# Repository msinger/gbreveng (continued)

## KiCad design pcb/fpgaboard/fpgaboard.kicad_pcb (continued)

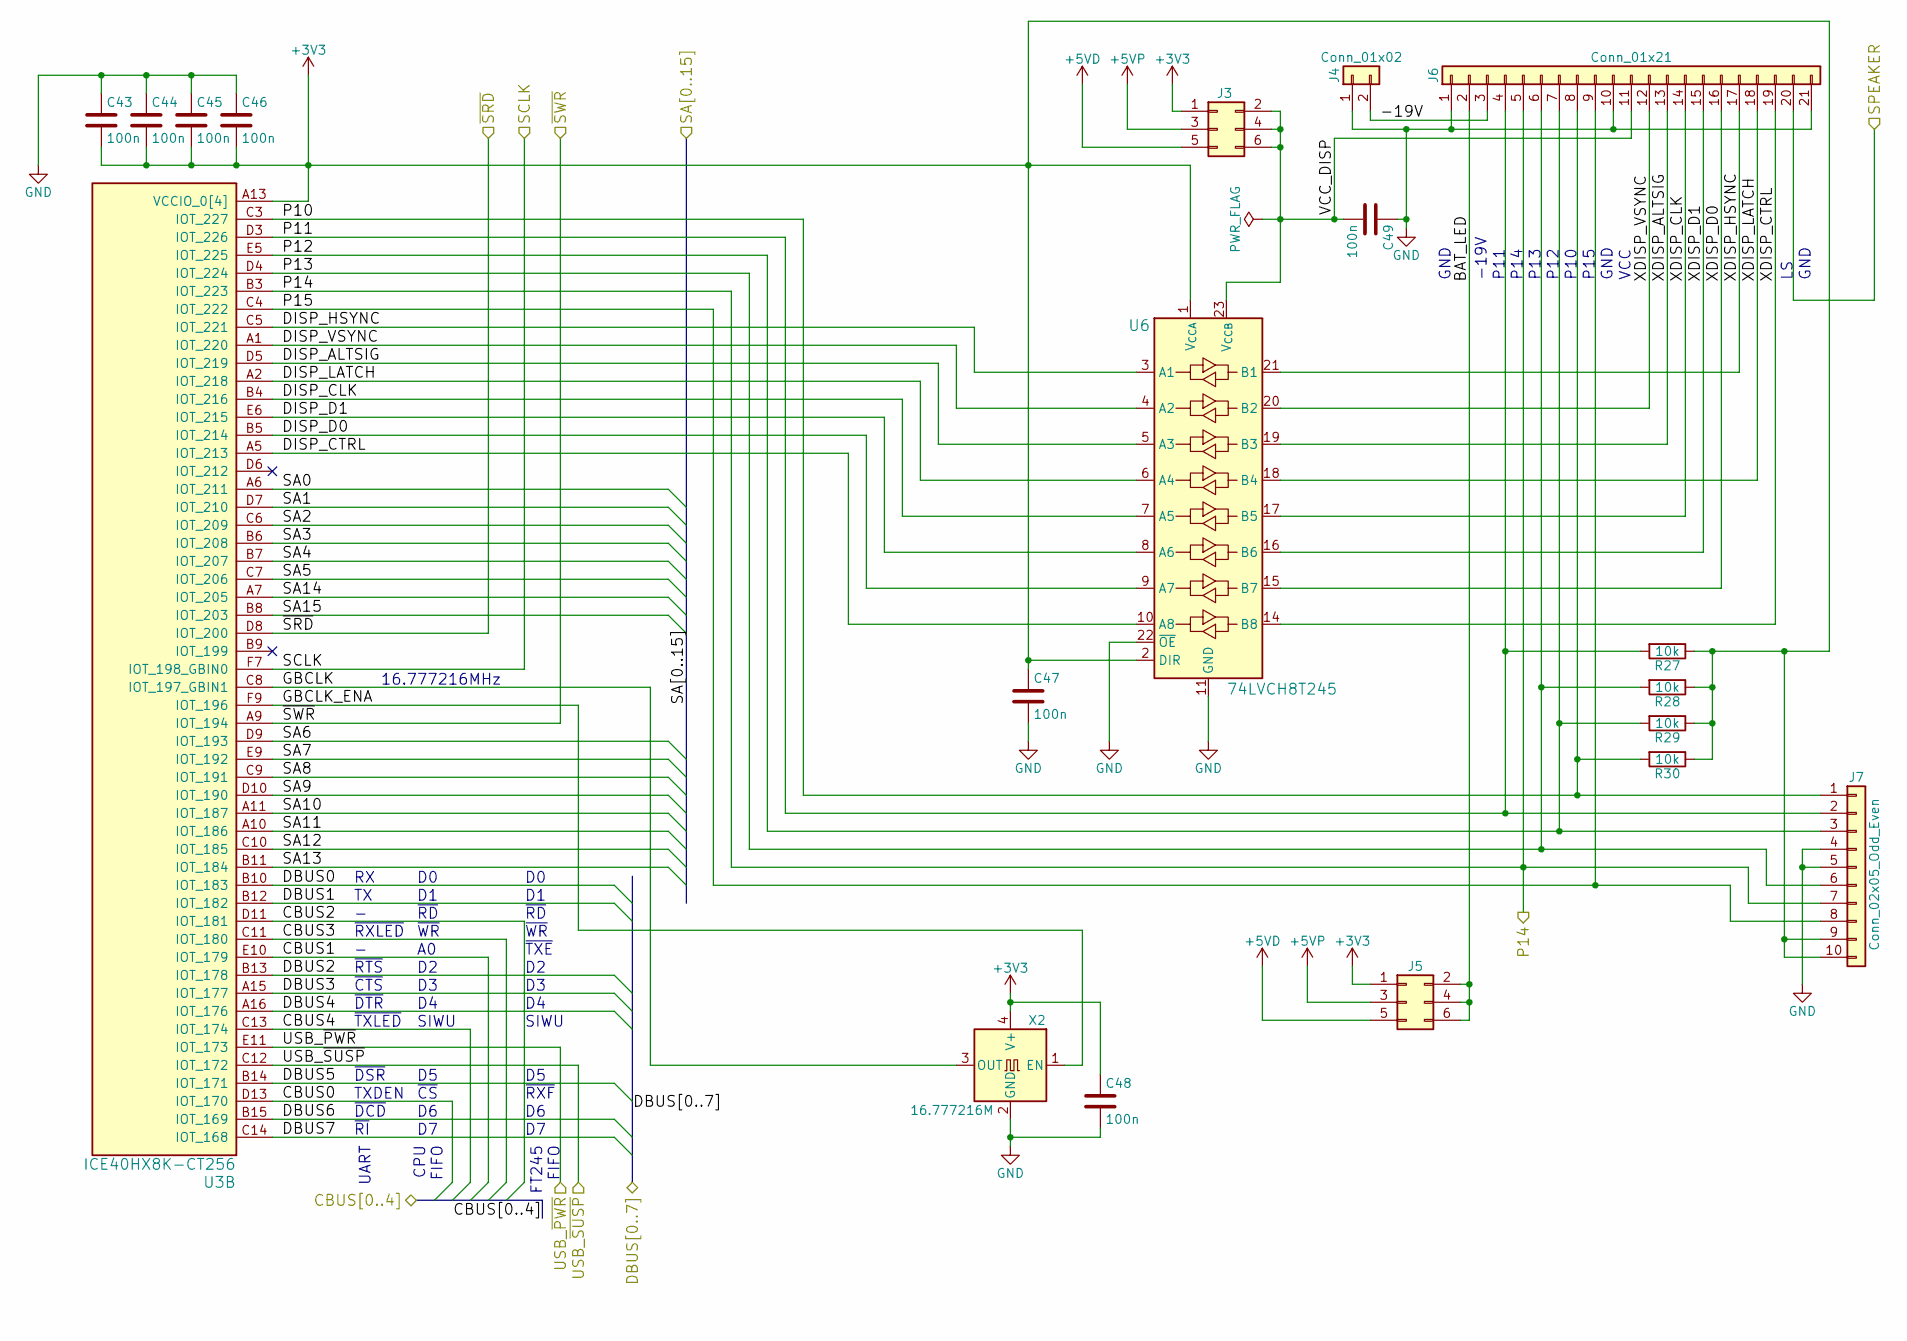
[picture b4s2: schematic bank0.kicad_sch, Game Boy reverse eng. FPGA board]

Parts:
C43, C44, C45, C46, C47, C48, C49: 100n; C_0402_1005Metric_Pad0.74x0.62mm_HandSolder
J3, J5: Conn_02x03_Odd_Even; PinHeader_2x03_P2.54mm_Vertical
J4: Conn_01x02; PinHeader_1x02_P2.54mm_Vertical
J6: Conn_01x21; DMG_FFC_LCD-Board_21Pin
J7: Conn_02x05_Odd_Even; PinHeader_2x05_P2.54mm_Vertical
R27, R28, R29, R30: 10k; R_0402_1005Metric
U3: ICE40HX8K-CT256; BGA-256_14.0x14.0mm_Layout16x16_P0.8mm_Ball0.45mm_Pad0.32mm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
U6: 74LVCH8T245; TSSOP-24_4.4x7.8mm_P0.65mm
X2: 16.777216M; Oscillator_SMD_EuroQuartz_XO32-4Pin_3.2x2.5mm_HandSoldering

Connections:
+3V3: C43.2, C44.2, C45.2, C46.2, C47.1, C48.1, J3.1, J5.1, J7.9, J7.10, R27.1, R28.1, R29.1, R30.1, U3.A3 (VCCIO_0[4]), U3.A8 (VCCIO_0[4]), U3.A13 (VCCIO_0[4]), U3.F8 (VCCIO_0[4]), U6.1 (V_{CCA}), U6.2 (DIR), X2.4 (V+); also elsewhere on the board
+5VD: J3.5, J5.5; also elsewhere on the board
+5VP: J3.3, J5.3; also elsewhere on the board
/Audio/SPEAKER: J6.20; also elsewhere on the board
/Bank0: Display, Keyboard, Clock/-19V: J4.2, J6.3
/Bank0: Display, Keyboard, Clock/A0: U3.A6 (IOT_211); also elsewhere on the board
/Bank0: Display, Keyboard, Clock/A1: U3.D7 (IOT_210); also elsewhere on the board
/Bank0: Display, Keyboard, Clock/A2: U3.C6 (IOT_209); also elsewhere on the board
/Bank0: Display, Keyboard, Clock/A3: U3.B6 (IOT_208); also elsewhere on the board
/Bank0: Display, Keyboard, Clock/A4: U3.B7 (IOT_207); also elsewhere on the board
/Bank0: Display, Keyboard, Clock/A5: U3.C7 (IOT_206); also elsewhere on the board
/Bank0: Display, Keyboard, Clock/A6: U3.D9 (IOT_193); also elsewhere on the board
/Bank0: Display, Keyboard, Clock/A7: U3.E9 (IOT_192); also elsewhere on the board
/Bank0: Display, Keyboard, Clock/A8: U3.C9 (IOT_191); also elsewhere on the board
/Bank0: Display, Keyboard, Clock/A9: U3.D10 (IOT_190); also elsewhere on the board
/Bank0: Display, Keyboard, Clock/A10: U3.A11 (IOT_187); also elsewhere on the board
/Bank0: Display, Keyboard, Clock/A11: U3.A10 (IOT_186); also elsewhere on the board
/Bank0: Display, Keyboard, Clock/A12: U3.C10 (IOT_185); also elsewhere on the board
/Bank0: Display, Keyboard, Clock/A13: U3.B11 (IOT_184); also elsewhere on the board
/Bank0: Display, Keyboard, Clock/A14: U3.A7 (IOT_205); also elsewhere on the board
/Bank0: Display, Keyboard, Clock/A15: U3.B8 (IOT_203); also elsewhere on the board
/Bank0: Display, Keyboard, Clock/BAT_LED: J5.2, J5.4, J5.6, J6.2
/Bank0: Display, Keyboard, Clock/CART_SL_CLK: U3.F7 (IOT_198_GBIN0); also elsewhere on the board
/Bank0: Display, Keyboard, Clock/CART_SL_~RD: U3.D8 (IOT_200); also elsewhere on the board
/Bank0: Display, Keyboard, Clock/CART_SL_~WR: U3.A9 (IOT_194); also elsewhere on the board
/Bank0: Display, Keyboard, Clock/CBUS0: U3.D13 (IOT_170); also elsewhere on the board
/Bank0: Display, Keyboard, Clock/CBUS1: U3.E10 (IOT_179); also elsewhere on the board
/Bank0: Display, Keyboard, Clock/CBUS2: U3.D11 (IOT_181); also elsewhere on the board
/Bank0: Display, Keyboard, Clock/CBUS3: U3.C11 (IOT_180); also elsewhere on the board
/Bank0: Display, Keyboard, Clock/CBUS4: U3.C13 (IOT_174); also elsewhere on the board
/Bank0: Display, Keyboard, Clock/DBUS0: U3.B10 (IOT_183); also elsewhere on the board
/Bank0: Display, Keyboard, Clock/DBUS1: U3.B12 (IOT_182); also elsewhere on the board
/Bank0: Display, Keyboard, Clock/DBUS2: U3.B13 (IOT_178); also elsewhere on the board
/Bank0: Display, Keyboard, Clock/DBUS3: U3.A15 (IOT_177); also elsewhere on the board
/Bank0: Display, Keyboard, Clock/DBUS4: U3.A16 (IOT_176); also elsewhere on the board
/Bank0: Display, Keyboard, Clock/DBUS5: U3.B14 (IOT_171); also elsewhere on the board
/Bank0: Display, Keyboard, Clock/DBUS6: U3.B15 (IOT_169); also elsewhere on the board
/Bank0: Display, Keyboard, Clock/DBUS7: U3.C14 (IOT_168); also elsewhere on the board
/Bank0: Display, Keyboard, Clock/DISP_ALTSIG: U3.D5 (IOT_219), U6.5 (A3)
/Bank0: Display, Keyboard, Clock/DISP_CLK: U3.B4 (IOT_216), U6.7 (A5)
/Bank0: Display, Keyboard, Clock/DISP_CTRL: U3.A5 (IOT_213), U6.10 (A8)
/Bank0: Display, Keyboard, Clock/DISP_D0: U3.B5 (IOT_214), U6.9 (A7)
/Bank0: Display, Keyboard, Clock/DISP_D1: U3.E6 (IOT_215), U6.8 (A6)
/Bank0: Display, Keyboard, Clock/DISP_HSYNC: U3.C5 (IOT_221), U6.3 (A1)
/Bank0: Display, Keyboard, Clock/DISP_LATCH: U3.A2 (IOT_218), U6.6 (A4)
/Bank0: Display, Keyboard, Clock/DISP_VSYNC: U3.A1 (IOT_220), U6.4 (A2)
/Bank0: Display, Keyboard, Clock/GBCLK: U3.C8 (IOT_197_GBIN1), X2.3 (OUT)
/Bank0: Display, Keyboard, Clock/GBCLK_ENA: U3.F9 (IOT_196), X2.1 (EN)
/Bank0: Display, Keyboard, Clock/P10: J6.8, J7.1, R30.2, U3.C3 (IOT_227)
/Bank0: Display, Keyboard, Clock/P11: J6.4, J7.2, R27.2, U3.D3 (IOT_226)
/Bank0: Display, Keyboard, Clock/P12: J6.7, J7.3, R29.2, U3.E5 (IOT_225)
/Bank0: Display, Keyboard, Clock/P13: J6.6, J7.6, R28.2, U3.D4 (IOT_224)
/Bank0: Display, Keyboard, Clock/P14: J6.5, J7.7, U3.B3 (IOT_223); also elsewhere on the board
/Bank0: Display, Keyboard, Clock/P15: J6.9, J7.8, U3.C4 (IOT_222)
/Bank0: Display, Keyboard, Clock/USB_~PWR: U3.E11 (IOT_173); also elsewhere on the board
/Bank0: Display, Keyboard, Clock/USB_~SUSP: U3.C12 (IOT_172); also elsewhere on the board
/Bank0: Display, Keyboard, Clock/VCC_DISP: C49.2, J3.2, J3.4, J3.6, J6.11, U6.23 (V_{CCB}), U6.24 (V_{CCB})
/Bank0: Display, Keyboard, Clock/XDISP_ALTSIG: J6.13, U6.19 (B3)
/Bank0: Display, Keyboard, Clock/XDISP_CLK: J6.14, U6.17 (B5)
/Bank0: Display, Keyboard, Clock/XDISP_CTRL: J6.19, U6.14 (B8)
/Bank0: Display, Keyboard, Clock/XDISP_D0: J6.16, U6.15 (B7)
/Bank0: Display, Keyboard, Clock/XDISP_D1: J6.15, U6.16 (B6)
/Bank0: Display, Keyboard, Clock/XDISP_HSYNC: J6.17, U6.21 (B1)
/Bank0: Display, Keyboard, Clock/XDISP_LATCH: J6.18, U6.18 (B4)
/Bank0: Display, Keyboard, Clock/XDISP_VSYNC: J6.12, U6.20 (B2)
GND: C43.1, C44.1, C45.1, C46.1, C47.2, C48.2, C49.1, J4.1, J6.1, J6.10, J6.21, J7.4, J7.5, U6.11 (GND), U6.12 (GND), U6.13 (GND), U6.22 (~OE), X2.2 (GND); also elsewhere on the board

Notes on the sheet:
~{TXLED}
~{WR}
~{RXLED}
~{RI}
CPU FIFO
SIWU
16.777216MHz
P11
P12
-19V
VCC
FT245 FIFO
GND
~{DSR}
~{RTS}
~{DCD}
~{DTR}
P14
~{CTS}
P15
UART
~{RD}
~{CS}
TXDEN
~{RXF}
~{TXE}
P13
P10

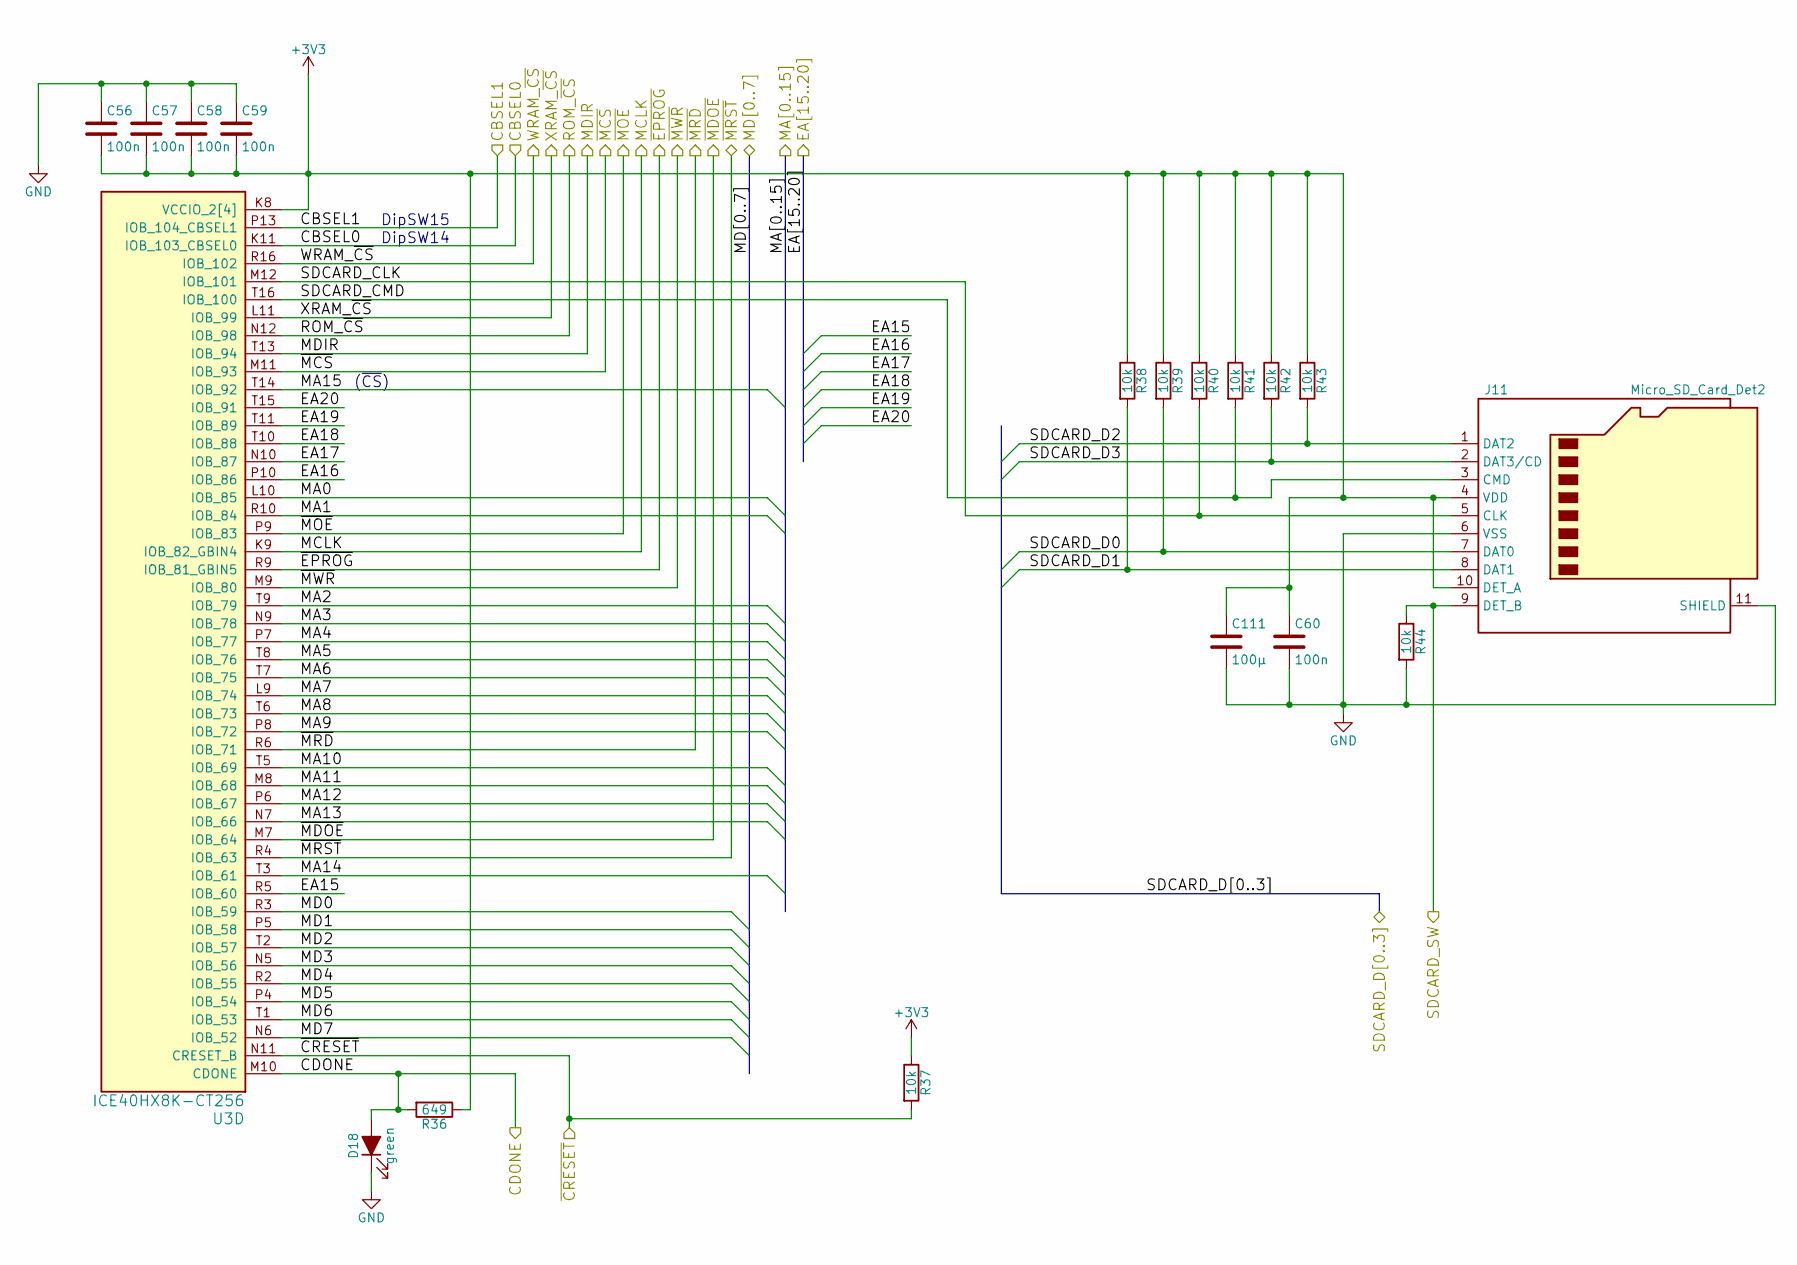
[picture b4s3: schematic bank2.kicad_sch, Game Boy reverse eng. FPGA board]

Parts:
C56, C57, C58, C59, C60: 100n; C_0402_1005Metric_Pad0.74x0.62mm_HandSolder
C111: 100µ; C_1206_3216Metric
D18: green; LED_0805_2012Metric_Pad1.15x1.40mm_HandSolder
J11: Micro_SD_Card_Det2; microSD_HC_Hirose_DM3AT-SF-PEJM5
R36: 649; R_0402_1005Metric
R37, R38, R39, R40, R41, R42, R43, R44: 10k; R_0402_1005Metric
U3: ICE40HX8K-CT256; BGA-256_14.0x14.0mm_Layout16x16_P0.8mm_Ball0.45mm_Pad0.32mm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

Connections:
+3V3: C56.2, C57.2, C58.2, C59.2, C60.1, C111.1, J11.4 (VDD), J11.10 (DET_A), R36.1, R37.1, R38.1, R39.1, R40.1, R41.1, R42.1, R43.1, U3.K8 (VCCIO_2[4]), U3.P3 (VCCIO_2[4]), U3.R8 (VCCIO_2[4]), U3.R13 (VCCIO_2[4]); also elsewhere on the board
/Bank1: GPIOA/SDCARD_SW: J11.9 (DET_B), R44.1; also elsewhere on the board
/Bank2: SDCard/CART_MA_CLK: U3.K9 (IOB_82_GBIN4); also elsewhere on the board
/Bank2: SDCard/CART_MA_DIR: U3.T13 (IOB_94); also elsewhere on the board
/Bank2: SDCard/CART_MA_~CS: U3.M11 (IOB_93); also elsewhere on the board
/Bank2: SDCard/CART_MA_~OE: U3.P9 (IOB_83); also elsewhere on the board
/Bank2: SDCard/CART_MA_~OE~_DATA: U3.M7 (IOB_64); also elsewhere on the board
/Bank2: SDCard/CART_MA_~RST: U3.R4 (IOB_63); also elsewhere on the board
/Bank2: SDCard/CBSEL0: U3.K11 (IOB_103_CBSEL0); also elsewhere on the board
/Bank2: SDCard/CBSEL1: U3.P13 (IOB_104_CBSEL1); also elsewhere on the board
/Bank2: SDCard/CDONE: D18.2 (A), R36.2, U3.M10 (CDONE); also elsewhere on the board
/Bank2: SDCard/EA15: U3.R5 (IOB_60); also elsewhere on the board
/Bank2: SDCard/EA16: U3.P10 (IOB_86); also elsewhere on the board
/Bank2: SDCard/EA17: U3.N10 (IOB_87); also elsewhere on the board
/Bank2: SDCard/EA18: U3.T10 (IOB_88); also elsewhere on the board
/Bank2: SDCard/EA19: U3.T11 (IOB_89); also elsewhere on the board
/Bank2: SDCard/EA20: U3.T15 (IOB_91); also elsewhere on the board
/Bank2: SDCard/MA0: U3.L10 (IOB_85); also elsewhere on the board
/Bank2: SDCard/MA1: U3.R10 (IOB_84); also elsewhere on the board
/Bank2: SDCard/MA2: U3.T9 (IOB_79); also elsewhere on the board
/Bank2: SDCard/MA3: U3.N9 (IOB_78); also elsewhere on the board
/Bank2: SDCard/MA4: U3.P7 (IOB_77); also elsewhere on the board
/Bank2: SDCard/MA5: U3.T8 (IOB_76); also elsewhere on the board
/Bank2: SDCard/MA6: U3.T7 (IOB_75); also elsewhere on the board
/Bank2: SDCard/MA7: U3.L9 (IOB_74); also elsewhere on the board
/Bank2: SDCard/MA8: U3.T6 (IOB_73); also elsewhere on the board
/Bank2: SDCard/MA9: U3.P8 (IOB_72); also elsewhere on the board
/Bank2: SDCard/MA10: U3.T5 (IOB_69); also elsewhere on the board
/Bank2: SDCard/MA11: U3.M8 (IOB_68); also elsewhere on the board
/Bank2: SDCard/MA12: U3.P6 (IOB_67); also elsewhere on the board
/Bank2: SDCard/MA13: U3.N7 (IOB_66); also elsewhere on the board
/Bank2: SDCard/MA14: U3.T3 (IOB_61); also elsewhere on the board
/Bank2: SDCard/MA15: U3.T14 (IOB_92); also elsewhere on the board
/Bank2: SDCard/MD0: U3.R3 (IOB_59); also elsewhere on the board
/Bank2: SDCard/MD1: U3.P5 (IOB_58); also elsewhere on the board
/Bank2: SDCard/MD2: U3.T2 (IOB_57); also elsewhere on the board
/Bank2: SDCard/MD3: U3.N5 (IOB_56); also elsewhere on the board
/Bank2: SDCard/MD4: U3.R2 (IOB_55); also elsewhere on the board
/Bank2: SDCard/MD5: U3.P4 (IOB_54); also elsewhere on the board
/Bank2: SDCard/MD6: U3.T1 (IOB_53); also elsewhere on the board
/Bank2: SDCard/MD7: U3.N6 (IOB_52); also elsewhere on the board
/Bank2: SDCard/ONBRD_~PROG: U3.R9 (IOB_81_GBIN5); also elsewhere on the board
/Bank2: SDCard/ROM_~CS: U3.N12 (IOB_98); also elsewhere on the board
/Bank2: SDCard/SD0: J11.7 (DAT0), R39.2; also elsewhere on the board
/Bank2: SDCard/SD1: J11.8 (DAT1), R38.2; also elsewhere on the board
/Bank2: SDCard/SD2: J11.1 (DAT2), R43.2; also elsewhere on the board
/Bank2: SDCard/SD3: J11.2 (DAT3/CD), R42.2; also elsewhere on the board
/Bank2: SDCard/SDCARD_CLK: J11.5 (CLK), R40.2, U3.M12 (IOB_101)
/Bank2: SDCard/SDCARD_CMD: J11.3 (CMD), R41.2, U3.T16 (IOB_100)
/Bank2: SDCard/WRAM_~CS: U3.R16 (IOB_102); also elsewhere on the board
/Bank2: SDCard/XRAM_~CS: U3.L11 (IOB_99); also elsewhere on the board
/Bank2: SDCard/~CRESET: R37.2, U3.N11 (CRESET_B); also elsewhere on the board
/~MRD: U3.R6 (IOB_71); also elsewhere on the board
/~MWR: U3.M9 (IOB_80); also elsewhere on the board
GND: C56.1, C57.1, C58.1, C59.1, C60.2, C111.2, D18.1 (K), J11.6 (VSS), J11.11 (SHIELD), R44.2; also elsewhere on the board

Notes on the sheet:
DipSW14
(~{CS})
DipSW15

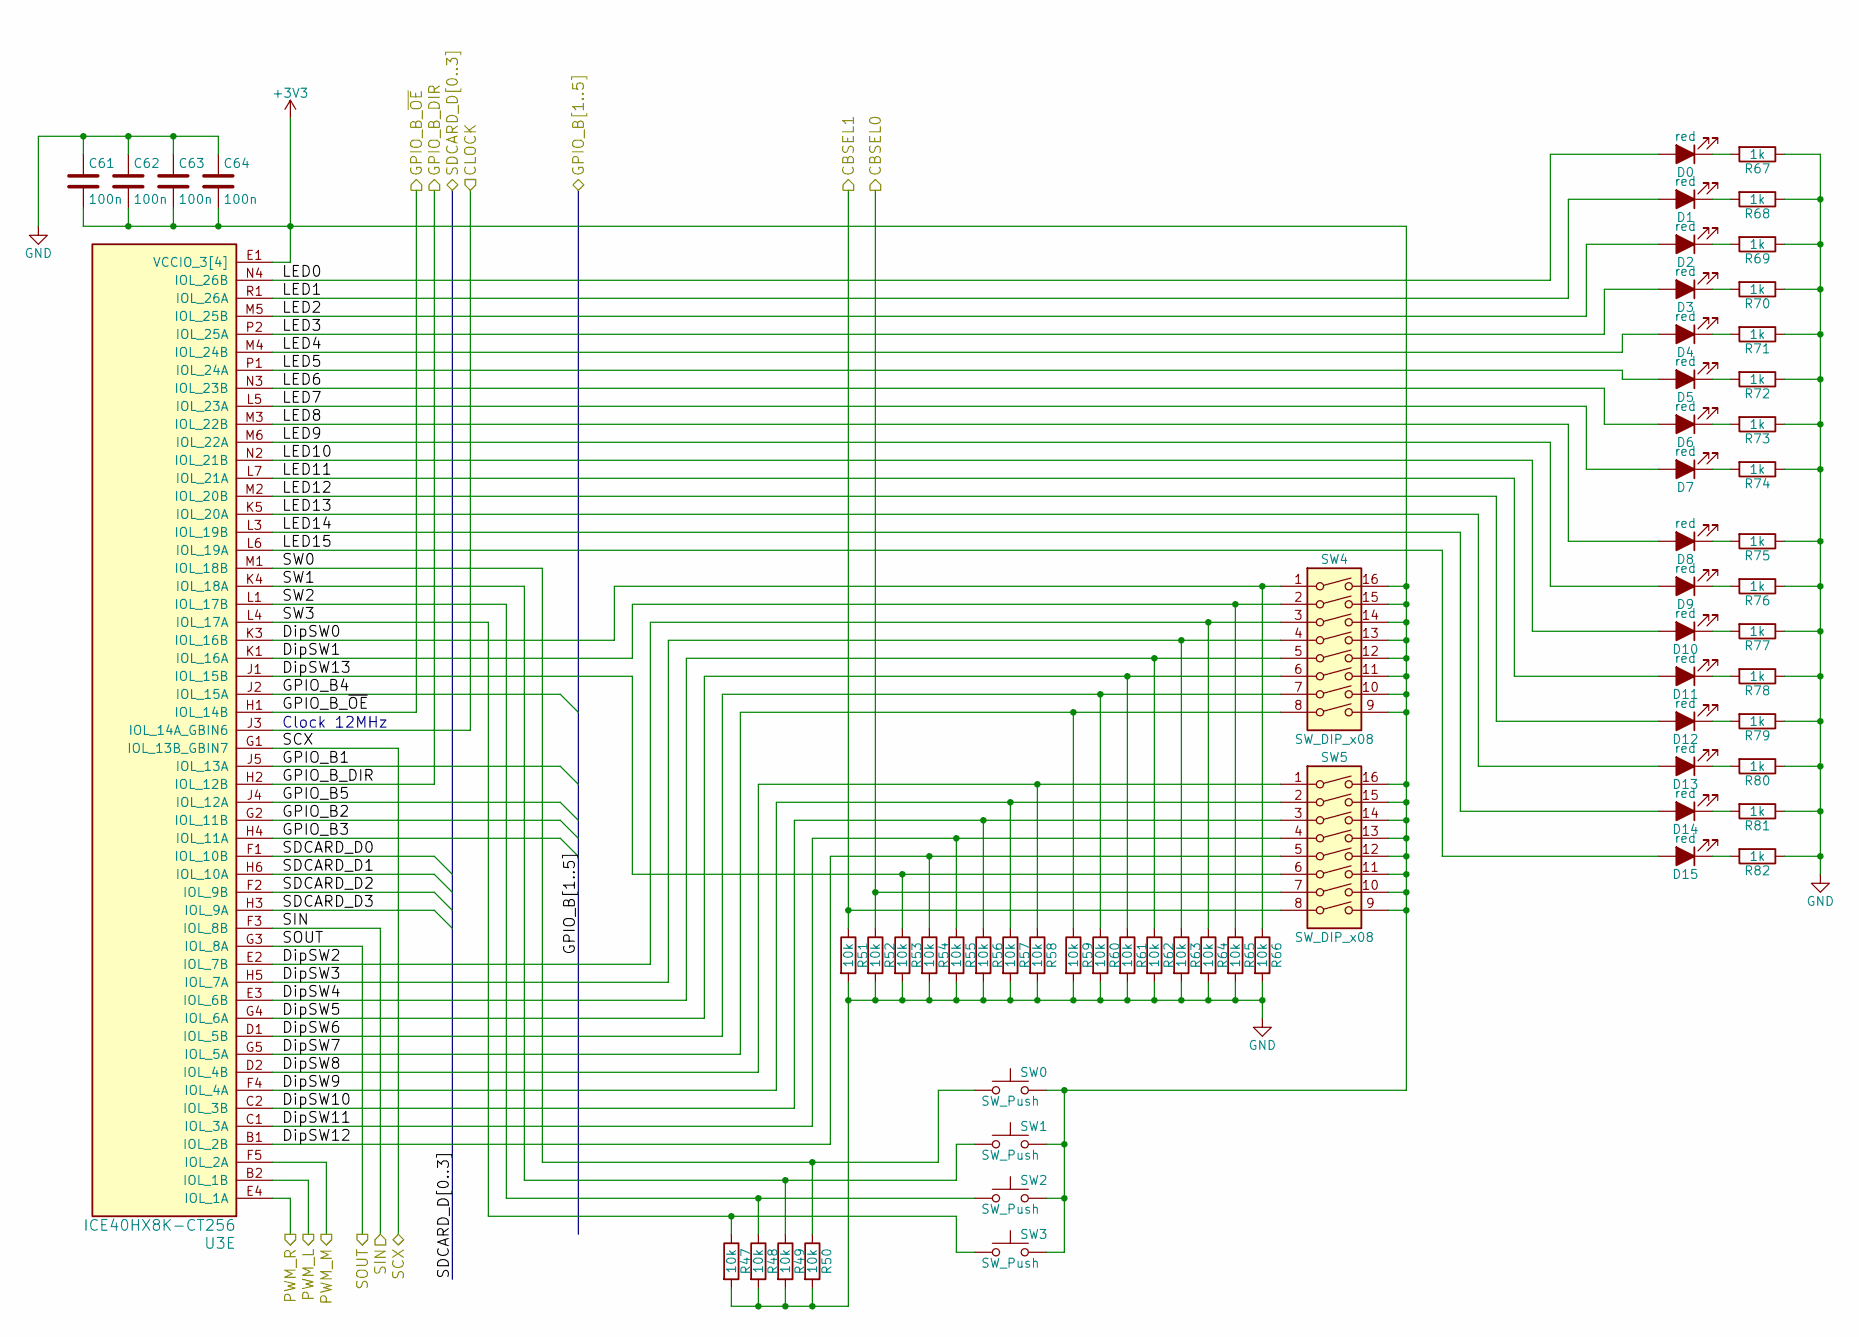
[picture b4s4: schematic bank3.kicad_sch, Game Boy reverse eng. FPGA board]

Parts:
C61, C62, C63, C64: 100n; C_0402_1005Metric_Pad0.74x0.62mm_HandSolder
D0, D1, D2, D3, D4, D5, D6, D7, D8, D9, D10, D11, D12, D13, D14, D15: red; LED_0805_2012Metric_Pad1.15x1.40mm_HandSolder
R47, R48, R49, R50, R51, R52, R53, R54, R55, R56, R57, R58, R59, R60, R61, R62, R63, R64, R65, R66: 10k; R_0402_1005Metric
R67, R68, R69, R70, R71, R72, R73, R74, R75, R76, R77, R78, R79, R80, R81, R82: 1k; R_0402_1005Metric
SW0, SW1, SW2, SW3: SW_Push; SW_SPST_B3U-1000P-B
SW4, SW5: SW_DIP_x08; SW_DIP_SPSTx08_Slide_9.78x22.5mm_W7.62mm_P2.54mm
U3: ICE40HX8K-CT256; BGA-256_14.0x14.0mm_Layout16x16_P0.8mm_Ball0.45mm_Pad0.32mm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

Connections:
+3V3: C61.2, C62.2, C63.2, C64.2, SW0.2, SW1.2, SW2.2, SW3.2, SW4.9, SW4.10, SW4.11, SW4.12, SW4.13, SW4.14, SW4.15, SW4.16, SW5.9, SW5.10, SW5.11, SW5.12, SW5.13, SW5.14, SW5.15, SW5.16, U3.E1 (VCCIO_3[4]), U3.G6 (VCCIO_3[4]), U3.J6 (VCCIO_3[4]), U3.N1 (VCCIO_3[4]); also elsewhere on the board
/Audio/PWM_L: U3.B2 (IOL_1B); also elsewhere on the board
/Audio/PWM_M: U3.F5 (IOL_2A); also elsewhere on the board
/Audio/PWM_R: U3.E4 (IOL_1A); also elsewhere on the board
/Bank2: SDCard/CBSEL0: R52.1, SW5.7; also elsewhere on the board
/Bank2: SDCard/CBSEL1: R51.1, SW5.8; also elsewhere on the board
/Bank2: SDCard/SD0: U3.F1 (IOL_10B); also elsewhere on the board
/Bank2: SDCard/SD1: U3.H6 (IOL_10A); also elsewhere on the board
/Bank2: SDCard/SD2: U3.F2 (IOL_9B); also elsewhere on the board
/Bank2: SDCard/SD3: U3.H3 (IOL_9A); also elsewhere on the board
/Bank3: LEDs, Switches/CLOCK: U3.J3 (IOL_14A_GBIN6); also elsewhere on the board
/Bank3: LEDs, Switches/DipSW0: R66.1, SW4.1, U3.K3 (IOL_16B)
/Bank3: LEDs, Switches/DipSW1: R65.1, SW4.2, U3.K1 (IOL_16A)
/Bank3: LEDs, Switches/DipSW2: R64.1, SW4.3, U3.E2 (IOL_7B)
/Bank3: LEDs, Switches/DipSW3: R63.1, SW4.4, U3.H5 (IOL_7A)
/Bank3: LEDs, Switches/DipSW4: R62.1, SW4.5, U3.E3 (IOL_6B)
/Bank3: LEDs, Switches/DipSW5: R61.1, SW4.6, U3.G4 (IOL_6A)
/Bank3: LEDs, Switches/DipSW6: R60.1, SW4.7, U3.D1 (IOL_5B)
/Bank3: LEDs, Switches/DipSW7: R59.1, SW4.8, U3.G5 (IOL_5A)
/Bank3: LEDs, Switches/DipSW8: R58.1, SW5.1, U3.D2 (IOL_4B)
/Bank3: LEDs, Switches/DipSW9: R57.1, SW5.2, U3.F4 (IOL_4A)
/Bank3: LEDs, Switches/DipSW10: R56.1, SW5.3, U3.C2 (IOL_3B)
/Bank3: LEDs, Switches/DipSW11: R55.1, SW5.4, U3.C1 (IOL_3A)
/Bank3: LEDs, Switches/DipSW12: R54.1, SW5.5, U3.B1 (IOL_2B)
/Bank3: LEDs, Switches/DipSW13: R53.1, SW5.6, U3.J1 (IOL_15B)
/Bank3: LEDs, Switches/GPIO_B1: U3.J5 (IOL_13A); also elsewhere on the board
/Bank3: LEDs, Switches/GPIO_B2: U3.G2 (IOL_11B); also elsewhere on the board
/Bank3: LEDs, Switches/GPIO_B3: U3.H4 (IOL_11A); also elsewhere on the board
/Bank3: LEDs, Switches/GPIO_B4: U3.J2 (IOL_15A); also elsewhere on the board
/Bank3: LEDs, Switches/GPIO_B5: U3.J4 (IOL_12A); also elsewhere on the board
/Bank3: LEDs, Switches/GPIO_B_~OE: U3.H1 (IOL_14B); also elsewhere on the board
/Bank3: LEDs, Switches/LED0: D0.2 (A), U3.N4 (IOL_26B)
/Bank3: LEDs, Switches/LED1: D1.2 (A), U3.R1 (IOL_26A)
/Bank3: LEDs, Switches/LED2: D2.2 (A), U3.M5 (IOL_25B)
/Bank3: LEDs, Switches/LED3: D3.2 (A), U3.P2 (IOL_25A)
/Bank3: LEDs, Switches/LED4: D4.2 (A), U3.M4 (IOL_24B)
/Bank3: LEDs, Switches/LED5: D5.2 (A), U3.P1 (IOL_24A)
/Bank3: LEDs, Switches/LED6: D6.2 (A), U3.N3 (IOL_23B)
/Bank3: LEDs, Switches/LED7: D7.2 (A), U3.L5 (IOL_23A)
/Bank3: LEDs, Switches/LED8: D8.2 (A), U3.M3 (IOL_22B)
/Bank3: LEDs, Switches/LED9: D9.2 (A), U3.M6 (IOL_22A)
/Bank3: LEDs, Switches/LED10: D10.2 (A), U3.N2 (IOL_21B)
/Bank3: LEDs, Switches/LED11: D11.2 (A), U3.L7 (IOL_21A)
/Bank3: LEDs, Switches/LED12: D12.2 (A), U3.M2 (IOL_20B)
/Bank3: LEDs, Switches/LED13: D13.2 (A), U3.K5 (IOL_20A)
/Bank3: LEDs, Switches/LED14: D14.2 (A), U3.L3 (IOL_19B)
/Bank3: LEDs, Switches/LED15: D15.2 (A), U3.L6 (IOL_19A)
/Bank3: LEDs, Switches/SCX: U3.G1 (IOL_13B_GBIN7); also elsewhere on the board
/Bank3: LEDs, Switches/SOUT: U3.G3 (IOL_8A); also elsewhere on the board
/Bank3: LEDs, Switches/SW0: R50.1, SW0.1, U3.M1 (IOL_18B)
/Bank3: LEDs, Switches/SW1: R49.1, SW1.1, U3.K4 (IOL_18A)
/Bank3: LEDs, Switches/SW2: R48.1, SW2.1, U3.L1 (IOL_17B)
/Bank3: LEDs, Switches/SW3: R47.1, SW3.1, U3.L4 (IOL_17A)
/External Link Port, GPIOB/DIR: U3.H2 (IOL_12B); also elsewhere on the board
/SIN: U3.F3 (IOL_8B); also elsewhere on the board
GND: C61.1, C62.1, C63.1, C64.1, R47.2, R48.2, R49.2, R50.2, R51.2, R52.2, R53.2, R54.2, R55.2, R56.2, R57.2, R58.2, R59.2, R60.2, R61.2, R62.2, R63.2, R64.2, R65.2, R66.2, R67.1, R68.1, R69.1, R70.1, R71.1, R72.1, R73.1, R74.1, R75.1, R76.1, R77.1, R78.1, R79.1, R80.1, R81.1, R82.1; also elsewhere on the board
unnamed: D0.1 (K), R67.2
unnamed: D1.1 (K), R68.2
unnamed: D2.1 (K), R69.2
unnamed: D3.1 (K), R70.2
unnamed: D4.1 (K), R71.2
unnamed: D5.1 (K), R72.2
unnamed: D6.1 (K), R73.2
unnamed: D7.1 (K), R74.2
unnamed: D8.1 (K), R75.2
unnamed: D9.1 (K), R76.2
unnamed: D10.1 (K), R77.2
unnamed: D11.1 (K), R78.2
unnamed: D12.1 (K), R79.2
unnamed: D13.1 (K), R80.2
unnamed: D14.1 (K), R81.2
unnamed: D15.1 (K), R82.2

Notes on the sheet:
Clock 12MHz

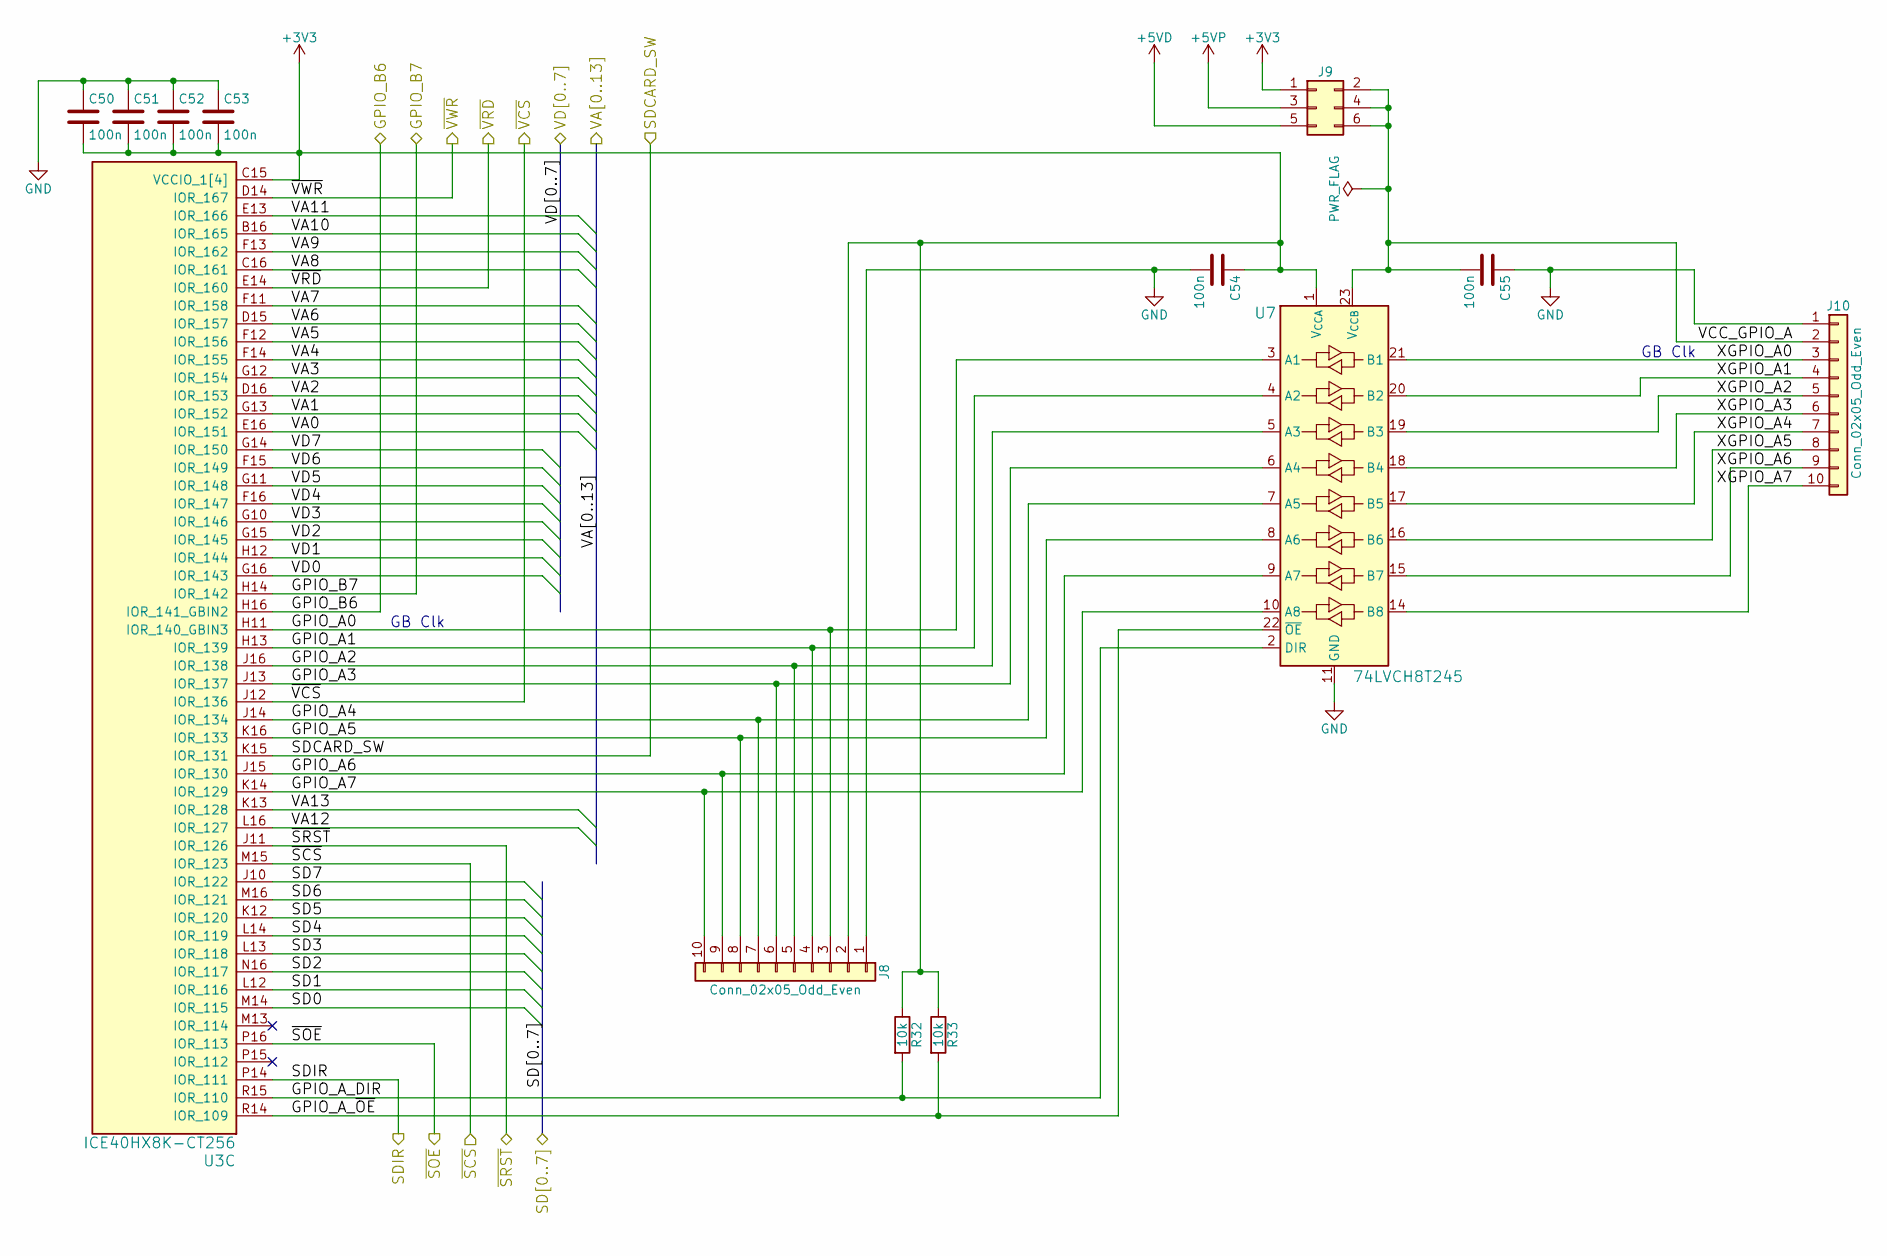
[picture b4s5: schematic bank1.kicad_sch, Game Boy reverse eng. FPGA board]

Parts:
C50, C51, C52, C53, C54, C55: 100n; C_0402_1005Metric_Pad0.74x0.62mm_HandSolder
J8, J10: Conn_02x05_Odd_Even; PinHeader_2x05_P2.54mm_Vertical
J9: Conn_02x03_Odd_Even; PinHeader_2x03_P2.54mm_Vertical
R32, R33: 10k; R_0402_1005Metric
U3: ICE40HX8K-CT256; BGA-256_14.0x14.0mm_Layout16x16_P0.8mm_Ball0.45mm_Pad0.32mm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
U7: 74LVCH8T245; TSSOP-24_4.4x7.8mm_P0.65mm

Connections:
+3V3: C50.2, C51.2, C52.2, C53.2, C54.1, J8.2, J9.1, R32.1, R33.1, U3.C15 (VCCIO_1[4]), U3.H10 (VCCIO_1[4]), U3.H15 (VCCIO_1[4]), U3.N15 (VCCIO_1[4]), U7.1 (V_{CCA}); also elsewhere on the board
+5VD: J9.5; also elsewhere on the board
+5VP: J9.3; also elsewhere on the board
/Bank1: GPIOA/CART_SL_DIR: U3.P14 (IOR_111); also elsewhere on the board
/Bank1: GPIOA/CART_SL_~CS: U3.M15 (IOR_123); also elsewhere on the board
/Bank1: GPIOA/CART_SL_~OE: U3.P16 (IOR_113); also elsewhere on the board
/Bank1: GPIOA/CART_SL_~RST: U3.J11 (IOR_126); also elsewhere on the board
/Bank1: GPIOA/D0: U3.M14 (IOR_115); also elsewhere on the board
/Bank1: GPIOA/D1: U3.L12 (IOR_116); also elsewhere on the board
/Bank1: GPIOA/D2: U3.N16 (IOR_117); also elsewhere on the board
/Bank1: GPIOA/D3: U3.L13 (IOR_118); also elsewhere on the board
/Bank1: GPIOA/D4: U3.L14 (IOR_119); also elsewhere on the board
/Bank1: GPIOA/D5: U3.K12 (IOR_120); also elsewhere on the board
/Bank1: GPIOA/D6: U3.M16 (IOR_121); also elsewhere on the board
/Bank1: GPIOA/D7: U3.J10 (IOR_122); also elsewhere on the board
/Bank1: GPIOA/GPIO_A0: J8.3, U3.H11 (IOR_140_GBIN3), U7.3 (A1)
/Bank1: GPIOA/GPIO_A1: J8.4, U3.H13 (IOR_139), U7.4 (A2)
/Bank1: GPIOA/GPIO_A2: J8.5, U3.J16 (IOR_138), U7.5 (A3)
/Bank1: GPIOA/GPIO_A3: J8.6, U3.J13 (IOR_137), U7.6 (A4)
/Bank1: GPIOA/GPIO_A4: J8.7, U3.J14 (IOR_134), U7.7 (A5)
/Bank1: GPIOA/GPIO_A5: J8.8, U3.K16 (IOR_133), U7.8 (A6)
/Bank1: GPIOA/GPIO_A6: J8.9, U3.J15 (IOR_130), U7.9 (A7)
/Bank1: GPIOA/GPIO_A7: J8.10, U3.K14 (IOR_129), U7.10 (A8)
/Bank1: GPIOA/GPIO_A_DIR: R32.2, U3.R15 (IOR_110), U7.2 (DIR)
/Bank1: GPIOA/GPIO_A_~OE: R33.2, U3.R14 (IOR_109), U7.22 (~OE)
/Bank1: GPIOA/SDCARD_SW: U3.K15 (IOR_131); also elsewhere on the board
/Bank1: GPIOA/VA0: U3.E16 (IOR_151); also elsewhere on the board
/Bank1: GPIOA/VA1: U3.G13 (IOR_152); also elsewhere on the board
/Bank1: GPIOA/VA2: U3.D16 (IOR_153); also elsewhere on the board
/Bank1: GPIOA/VA3: U3.G12 (IOR_154); also elsewhere on the board
/Bank1: GPIOA/VA4: U3.F14 (IOR_155); also elsewhere on the board
/Bank1: GPIOA/VA5: U3.F12 (IOR_156); also elsewhere on the board
/Bank1: GPIOA/VA6: U3.D15 (IOR_157); also elsewhere on the board
/Bank1: GPIOA/VA7: U3.F11 (IOR_158); also elsewhere on the board
/Bank1: GPIOA/VA8: U3.C16 (IOR_161); also elsewhere on the board
/Bank1: GPIOA/VA9: U3.F13 (IOR_162); also elsewhere on the board
/Bank1: GPIOA/VA10: U3.B16 (IOR_165); also elsewhere on the board
/Bank1: GPIOA/VA11: U3.E13 (IOR_166); also elsewhere on the board
/Bank1: GPIOA/VA12: U3.L16 (IOR_127); also elsewhere on the board
/Bank1: GPIOA/VA13: U3.K13 (IOR_128); also elsewhere on the board
/Bank1: GPIOA/VCC_GPIO_A: C55.2, J9.2, J9.4, J9.6, J10.2, U7.23 (V_{CCB}), U7.24 (V_{CCB})
/Bank1: GPIOA/VD0: U3.G16 (IOR_143); also elsewhere on the board
/Bank1: GPIOA/VD1: U3.H12 (IOR_144); also elsewhere on the board
/Bank1: GPIOA/VD2: U3.G15 (IOR_145); also elsewhere on the board
/Bank1: GPIOA/VD3: U3.G10 (IOR_146); also elsewhere on the board
/Bank1: GPIOA/VD4: U3.F16 (IOR_147); also elsewhere on the board
/Bank1: GPIOA/VD5: U3.G11 (IOR_148); also elsewhere on the board
/Bank1: GPIOA/VD6: U3.F15 (IOR_149); also elsewhere on the board
/Bank1: GPIOA/VD7: U3.G14 (IOR_150); also elsewhere on the board
/Bank1: GPIOA/XGPIO_A0: J10.3, U7.21 (B1)
/Bank1: GPIOA/XGPIO_A1: J10.4, U7.20 (B2)
/Bank1: GPIOA/XGPIO_A2: J10.5, U7.19 (B3)
/Bank1: GPIOA/XGPIO_A3: J10.6, U7.18 (B4)
/Bank1: GPIOA/XGPIO_A4: J10.7, U7.17 (B5)
/Bank1: GPIOA/XGPIO_A5: J10.8, U7.16 (B6)
/Bank1: GPIOA/XGPIO_A6: J10.9, U7.15 (B7)
/Bank1: GPIOA/XGPIO_A7: J10.10, U7.14 (B8)
/GPIO_B6: U3.H16 (IOR_141_GBIN2); also elsewhere on the board
/GPIO_B7: U3.H14 (IOR_142); also elsewhere on the board
/~VCS: U3.J12 (IOR_136); also elsewhere on the board
/~VRD: U3.E14 (IOR_160); also elsewhere on the board
/~VWR: U3.D14 (IOR_167); also elsewhere on the board
GND: C50.1, C51.1, C52.1, C53.1, C54.2, C55.1, J8.1, J10.1, U7.11 (GND), U7.12 (GND), U7.13 (GND); also elsewhere on the board

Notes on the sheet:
GB Clk
